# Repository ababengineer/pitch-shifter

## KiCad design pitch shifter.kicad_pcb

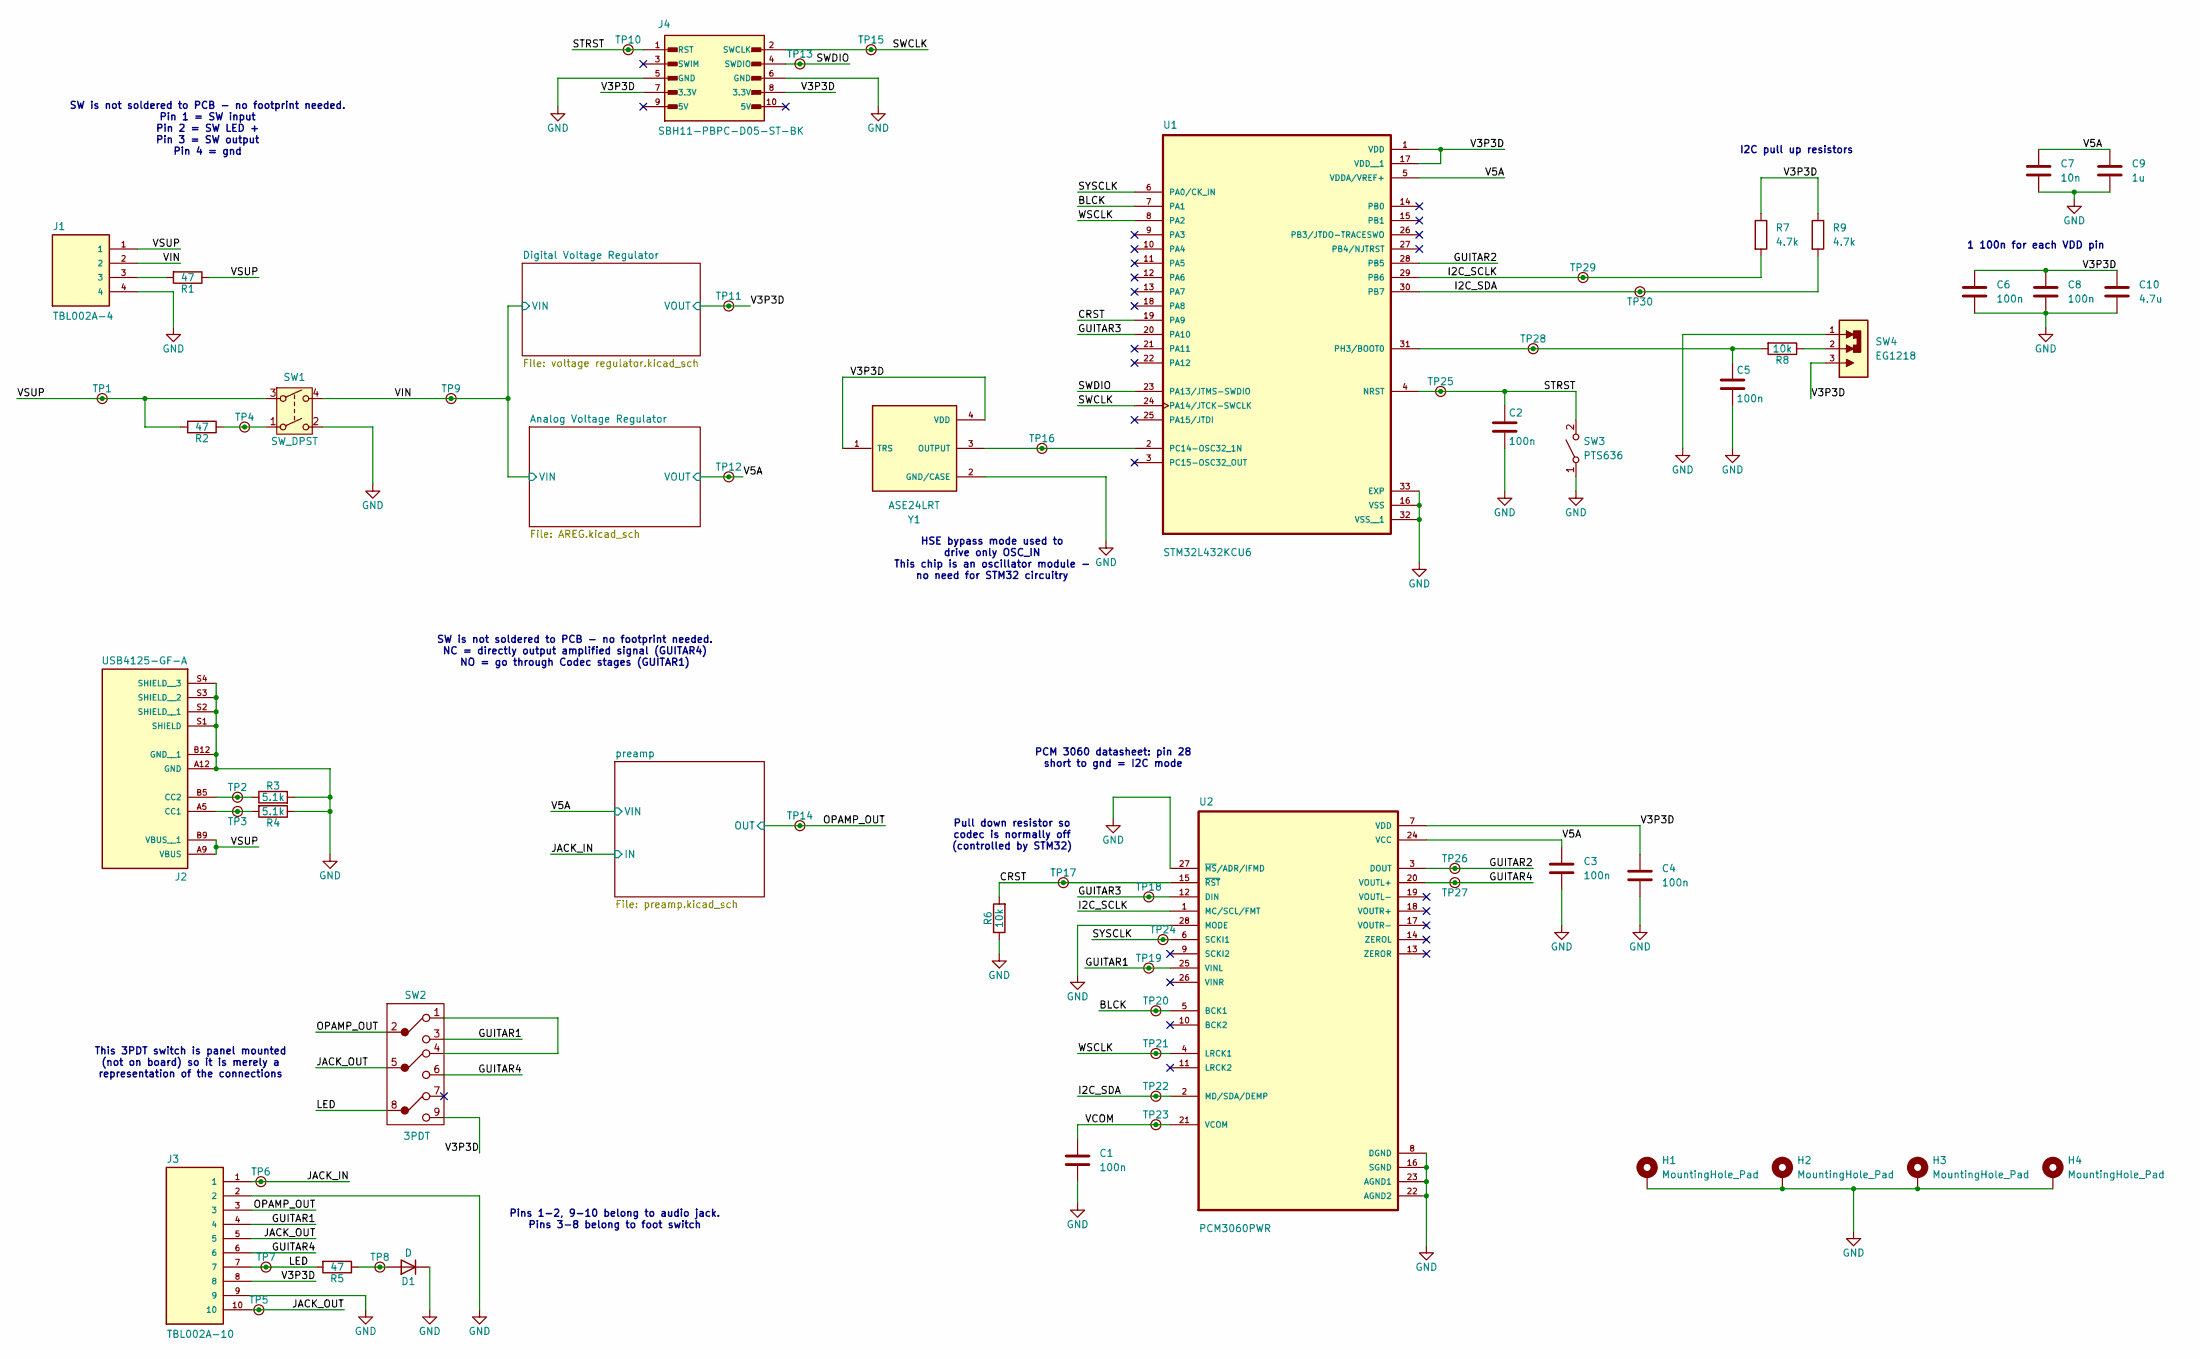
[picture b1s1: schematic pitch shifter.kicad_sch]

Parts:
C1, C2, C3, C4, C5, C6, C8: 100n; C_0603_1608Metric_Pad1.08x0.95mm_HandSolder
C7: 10n; C_0603_1608Metric_Pad1.08x0.95mm_HandSolder
C9: 1u; C_0603_1608Metric_Pad1.08x0.95mm_HandSolder
C10: 4.7u; C_0603_1608Metric_Pad1.08x0.95mm_HandSolder
D1: D; D_0603_1608Metric_Pad1.05x0.95mm_HandSolder
H1, H2, H3, H4: MountingHole_Pad; MountingHole_3.2mm_M3_Pad_Via
J1: TBL002A-4; PARTREV 1.0
J2: USB4125-GF-A; USB-C (power only); PARTREV Rev A2
J3: TBL002A-10; PARTREV 1.0
J4: SBH11-PBPC-D05-ST-BK; PARTREV J
R1, R2, R5: 47; R_0603_1608Metric_Pad0.98x0.95mm_HandSolder
R3, R4: 5.1k; R_0603_1608Metric_Pad0.98x0.95mm_HandSolder
R6, R8: 10k; R_0603_1608Metric_Pad0.98x0.95mm_HandSolder
R7, R9: 4.7k; R_0603_1608Metric_Pad0.98x0.95mm_HandSolder
SW1: SW_DPST
SW2: 3PDT
SW3: PTS636
SW4: EG1218
TP1, TP2, TP3, TP4, TP5, TP6, TP7, TP8, TP9, TP10, TP11, TP12, TP13, TP14, TP15, TP16, TP17, TP18, TP19, TP20, TP21, TP22, TP23, TP24, TP25, TP26, TP27, TP28, TP29, TP30: Test Point; TestPoint_THTPad_D1.0mm_Drill0.5mm
U1: STM32L432KCU6; PARTREV 3
U2: PCM3060PWR
Y1: ASE24LRT; PARTREV 02-18-22

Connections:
/BLCK: TP20.1, U1.7 (PA1), U2.5 (BCK1)
/CRST: R6.2, TP17.1, U1.19 (PA9), U2.15 (~RST)
/GUITAR1: J3.4, SW2.3, TP19.1, U2.25 (VINL)
/GUITAR2: TP26.1, U1.28 (PB5), U2.3 (DOUT)
/GUITAR3: TP18.1, U1.20 (PA10), U2.12 (DIN)
/GUITAR4: J3.6, SW2.6, TP27.1, U2.20 (VOUTL+)
/I2C_SCLK: R7.2, TP29.1, U1.29 (PB6), U2.1 (MC/SCL/FMT)
/I2C_SDA: R9.2, TP22.1, TP30.1, U1.30 (PB7), U2.2 (MD/SDA/DEMP)
/JACK_IN: J3.1, TP6.1; also elsewhere on the board
/JACK_OUT: J3.5, J3.10, SW2.5, TP5.1
/LED: J3.7, R5.2, SW2.8, TP7.1
/OPAMP_OUT: J3.3, SW2.2, TP14.1; also elsewhere on the board
/STRST: C2.1, J4.1 (RST), SW3.2 (B), TP10.1, TP25.1, U1.4 (NRST)
/SWCLK: J4.2 (SWCLK), TP15.1, U1.24 (PA14/JTCK-SWCLK)
/SWDIO: J4.4 (SWDIO), TP13.1, U1.23 (PA13/JTMS-SWDIO)
/SYSCLK: TP24.1, U1.6 (PA0/CK_IN), U2.6 (SCKI1)
/V3P3D: C4.1, C6.1, C8.1, C10.1, J3.8, J4.7 (3.3V), J4.8 (3.3V), R7.1, R9.1, SW2.9, SW4.3, TP11.1, U1.1 (VDD), U1.17 (VDD__1), U2.7 (VDD), Y1.1 (TRS), Y1.4 (VDD); also elsewhere on the board
/V5A: C3.1, C7.1, C9.1, TP12.1, U1.5 (VDDA/VREF+), U2.24 (VCC); also elsewhere on the board
/VCOM: C1.1, TP23.1, U2.21 (VCOM)
/VIN: J1.2, SW1.4, TP9.1; also elsewhere on the board
/VSUP: J1.1, J2.A9 (VBUS), J2.B9 (VBUS__1), R1.1, R2.2, SW1.3, TP1.1
/WSCLK: TP21.1, U1.8 (PA2), U2.4 (LRCK1)
GND: C1.2, C2.2, C3.2, C4.2, C5.2, C6.2, C7.2, C8.2, C9.2, C10.2, D1.1 (K), H1.1, H2.1, H3.1, H4.1, J1.4, J2.A12 (GND), J2.B12 (GND__1), J2.S1 (SHIELD), J2.S2 (SHIELD__1), J2.S3 (SHIELD__2), J2.S4 (SHIELD__3), J3.2, J3.9, J4.5 (GND), J4.6 (GND), R3.2, R4.1, R6.1, SW1.2, SW3.1 (A), SW4.1, U1.16 (VSS), U1.32 (VSS__1), U1.33 (EXP), U2.8 (DGND), U2.16 (SGND), U2.22 (AGND2), U2.23 (AGND1), U2.27 (~MS/ADR/IFMD), U2.28 (MODE), Y1.2 (GND/CASE); also elsewhere on the board
unnamed: D1.2 (A), R5.1, TP8.1
unnamed: J1.3, R1.2
unnamed: J2.A5 (CC1), R4.2, TP3.1
unnamed: J2.B5 (CC2), R3.1, TP2.1
unnamed: R2.1, SW1.1, TP4.1
unnamed: R8.1, SW4.2
unnamed: SW2.1, SW2.4
unnamed: TP16.1, U1.2 (PC14-OSC32_1N), Y1.3 (OUTPUT)
unnamed: C5.1, R8.2, TP28.1, U1.31 (PH3/BOOT0)

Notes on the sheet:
Pins 1-2, 9-10 belong to audio jack. Pins 3-8 belong to foot switch
Pull down resistor so codec is normally off (controlled by STM32)
SW is not soldered to PCB - no footprint needed. NC = directly output amplified signal (GUITAR4) NO = go through Codec stages (GUITAR1)
HSE bypass mode used to drive only OSC_IN This chip is an oscillator module - no need for STM32 circuitry
SW is not soldered to PCB - no footprint needed. Pin 1 = SW input Pin 2 = SW LED + Pin 3 = SW output Pin 4 = gnd
I2C pull up resistors
1 100n for each VDD pin
This 3PDT switch is panel mounted (not on board) so it is merely a representation of the connections
PCM 3060 datasheet: pin 28 short to gnd = I2C mode

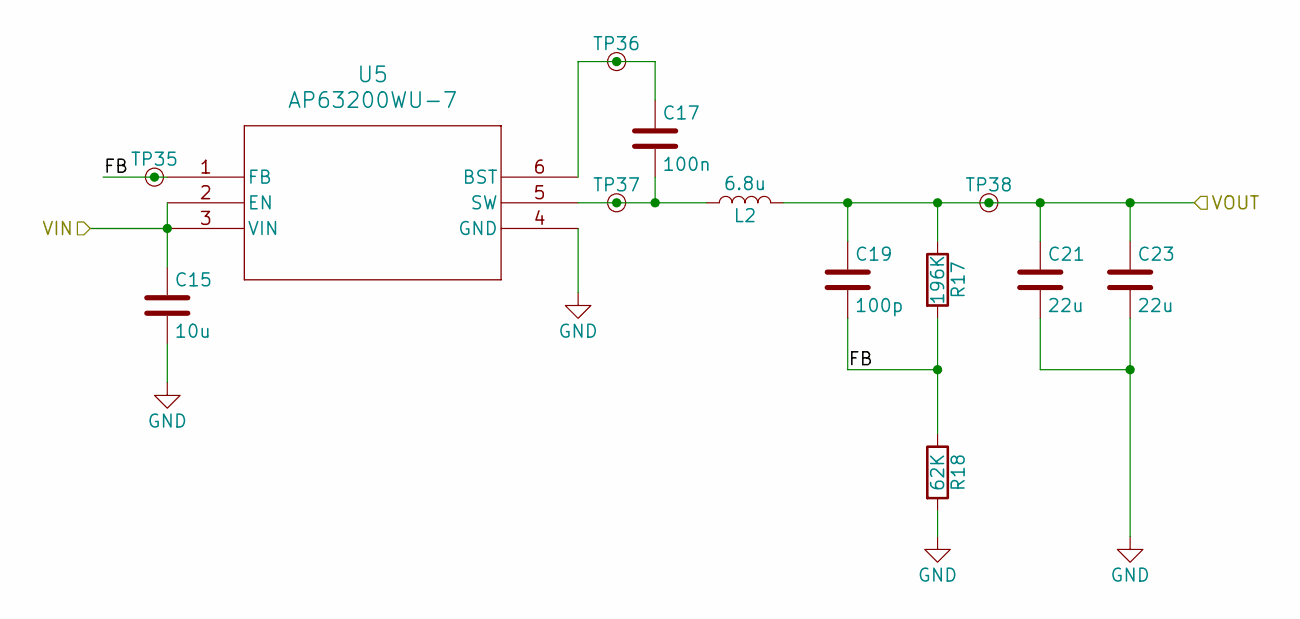
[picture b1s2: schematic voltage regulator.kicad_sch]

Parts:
C15: 10u; C_0603_1608Metric_Pad1.08x0.95mm_HandSolder
C17: 100n; C_0603_1608Metric_Pad1.08x0.95mm_HandSolder
C19: 100p; C_0603_1608Metric_Pad1.08x0.95mm_HandSolder
C21, C23: 22u; C_0603_1608Metric_Pad1.08x0.95mm_HandSolder
L2: 6.8u; L_0603_1608Metric_Pad1.05x0.95mm_HandSolder
R17: 196K; R_0603_1608Metric_Pad0.98x0.95mm_HandSolder
R18: 62K; R_0603_1608Metric_Pad0.98x0.95mm_HandSolder
TP35, TP36, TP37, TP38: Test Point; TestPoint_THTPad_D1.0mm_Drill0.5mm
U5: AP63200WU-7; AP63200WU_7

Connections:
/Digital Voltage Regulator/FB: C19.2, R17.2, R18.1, TP35.1, U5.1 (FB)
/V3P3D: C19.1, C21.1, C23.1, L2.2, R17.1, TP38.1; also elsewhere on the board
/VIN: C15.1, U5.2 (EN), U5.3 (VIN); also elsewhere on the board
GND: C15.2, C21.2, C23.2, R18.2, U5.4 (GND); also elsewhere on the board
unnamed: C17.1, TP36.1, U5.6 (BST)
unnamed: C17.2, L2.1, TP37.1, U5.5 (SW)

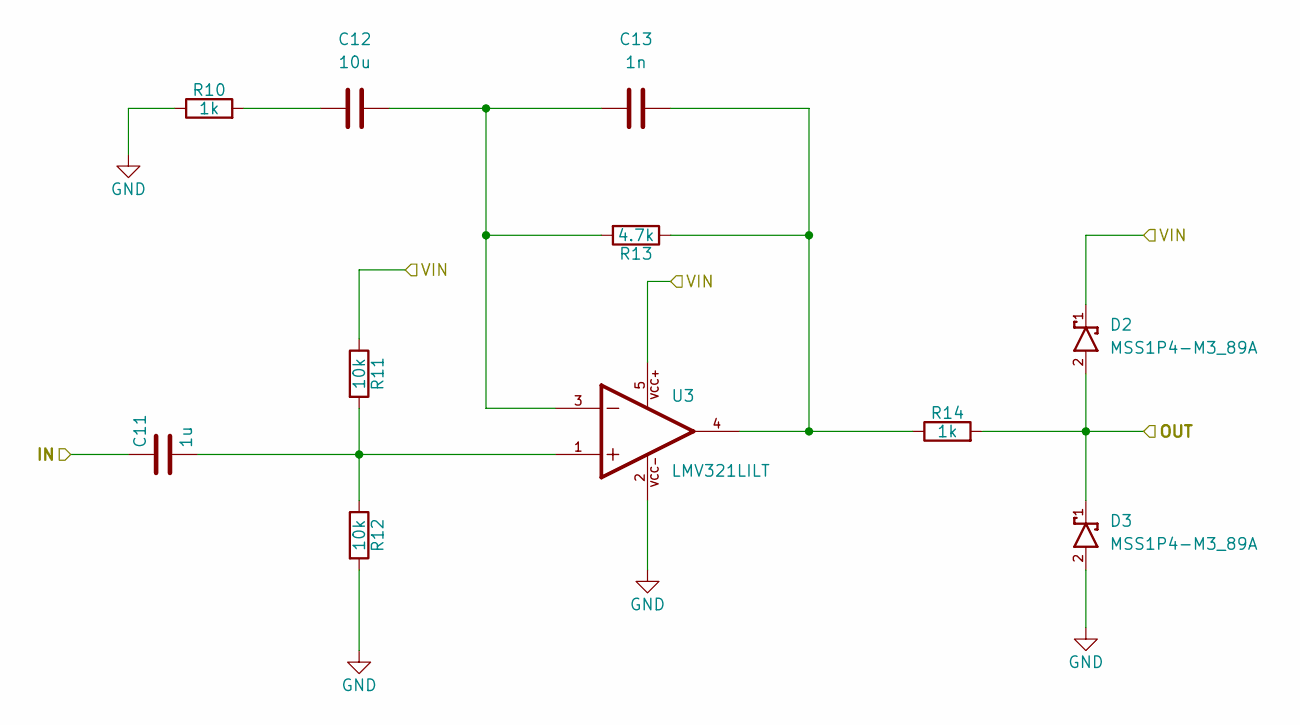
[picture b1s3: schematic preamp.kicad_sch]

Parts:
C11: 1u; C_0603_1608Metric_Pad1.08x0.95mm_HandSolder
C12: 10u; C_0603_1608Metric_Pad1.08x0.95mm_HandSolder
C13: 1n; C_0603_1608Metric_Pad1.08x0.95mm_HandSolder
D2, D3: MSS1P4-M3_89A
R10, R14: 1k; R_0603_1608Metric_Pad0.98x0.95mm_HandSolder
R11, R12: 10k; R_0603_1608Metric_Pad0.98x0.95mm_HandSolder
R13: 4.7k; R_0603_1608Metric_Pad0.98x0.95mm_HandSolder
U3: LMV321LILT; PARTREV 3

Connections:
/JACK_IN: C11.1; also elsewhere on the board
/OPAMP_OUT: D2.2, D3.1, R14.2; also elsewhere on the board
/V5A: D2.1, R11.1, U3.5; also elsewhere on the board
GND: D3.2, R10.1, R12.2, U3.2; also elsewhere on the board
unnamed: C11.2, R11.2, R12.1, U3.1
unnamed: C12.1, C13.2, R13.2, U3.3
unnamed: C12.2, R10.2
unnamed: C13.1, R13.1, R14.1, U3.4

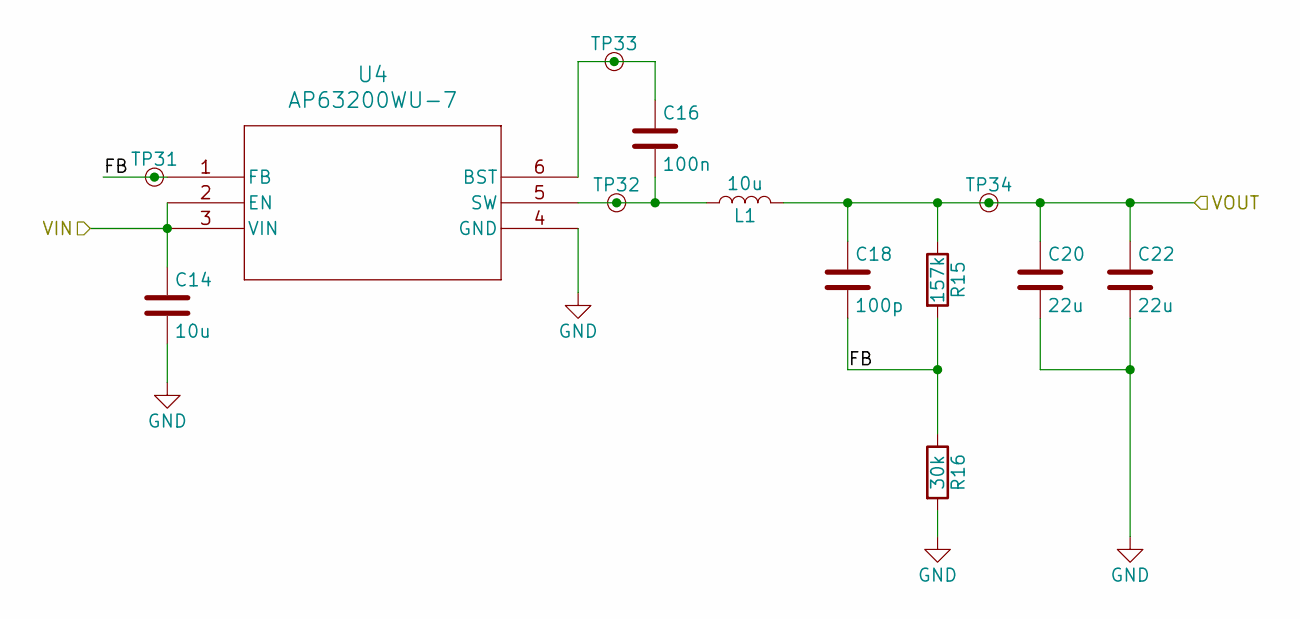
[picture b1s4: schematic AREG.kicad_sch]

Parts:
C14: 10u; C_0603_1608Metric_Pad1.08x0.95mm_HandSolder
C16: 100n; C_0603_1608Metric_Pad1.08x0.95mm_HandSolder
C18: 100p; C_0603_1608Metric_Pad1.08x0.95mm_HandSolder
C20, C22: 22u; C_0603_1608Metric_Pad1.08x0.95mm_HandSolder
L1: 10u; L_0603_1608Metric_Pad1.05x0.95mm_HandSolder
R15: 157k; R_0603_1608Metric_Pad0.98x0.95mm_HandSolder
R16: 30k; R_0603_1608Metric_Pad0.98x0.95mm_HandSolder
TP31, TP32, TP33, TP34: Test Point; TestPoint_THTPad_D1.0mm_Drill0.5mm
U4: AP63200WU-7; AP63200WU_7

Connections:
/Analog Voltage Regulator/FB: C18.2, R15.2, R16.1, TP31.1, U4.1 (FB)
/V5A: C18.1, C20.1, C22.1, L1.2, R15.1, TP34.1; also elsewhere on the board
/VIN: C14.1, U4.2 (EN), U4.3 (VIN); also elsewhere on the board
GND: C14.2, C20.2, C22.2, R16.2, U4.4 (GND); also elsewhere on the board
unnamed: C16.1, TP33.1, U4.6 (BST)
unnamed: C16.2, L1.1, TP32.1, U4.5 (SW)

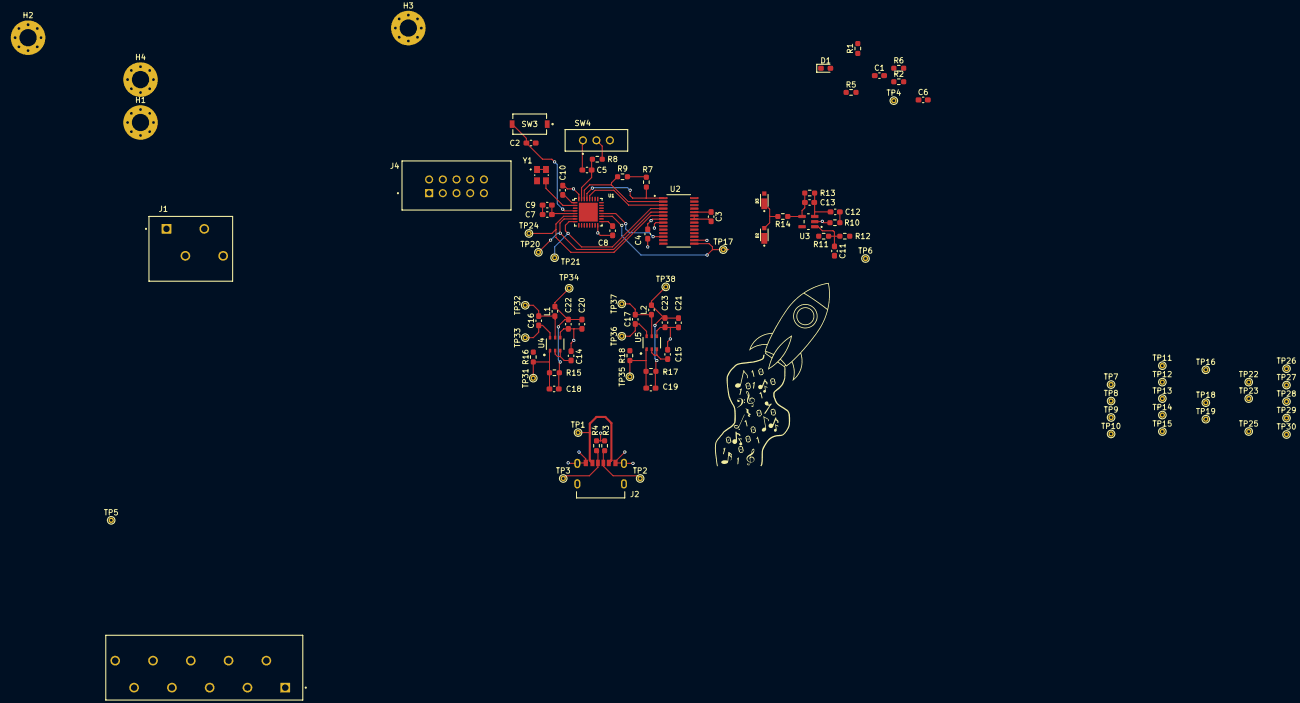
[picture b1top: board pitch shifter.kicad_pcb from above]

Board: 2 copper layers, 101 parts (0 on the bottom side), 41 nets.

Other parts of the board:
G**: LOGO

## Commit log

2026-02-15 added power and output switches
2026-02-16 Add oscillator, mounting holes, switches
2026-02-18 Added analog supply, finished codec wiring, added audio jacks
2026-02-19 swap stm32 with SAI compatible and add new molex connector
2026-02-25 Complete pre-amp and pre-amp sim
2026-02-28 Began board layout
